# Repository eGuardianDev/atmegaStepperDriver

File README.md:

# atmegaStepperDriver  
  Open source stepper driver powered by Atmega chip

## Quick Description
This project was design to be used in my [Modul3D](https://github.com/eGuardianDev/Modul3D) project.
Now It has its own project.  
The idea to have simple, cheap, open source stepper driver for stepper motor

## Features and design   
- Powered by Atmega chip (at the moment Atmega328)  
- H-Bridge design  
- Flyback Voltage protection  
- Standart stepper driver communication  
- I2C communcation interface
- Fan controll

## Current Development
### Firmware
 - [ ] Todo...
### Hardware
#### Power
- [X] Power supply for the chip
- [X] Sepreate connection for power for the motor
- [X] Pins for power
#### Main system
- [X] H-bridge configuration
- [X] Connect the pins to the transistor of H-bridge
- [X] Calculate transistor resistor values
#### Communication
- [X] Pins for communication
- [X] I2C pins
- [X] Address Changer
- [ ] Step mode (maybe in next version or firmware based)
#### Protection
- [X] Add capacitor before transitor for smooth curves, but don't test it
- [X] Flyback protection (with ziner diode) 
- [X] Power supply smoothing and return diode
- [ ] Fully test protection system
#### Misc.
- [X] Change diode foot print

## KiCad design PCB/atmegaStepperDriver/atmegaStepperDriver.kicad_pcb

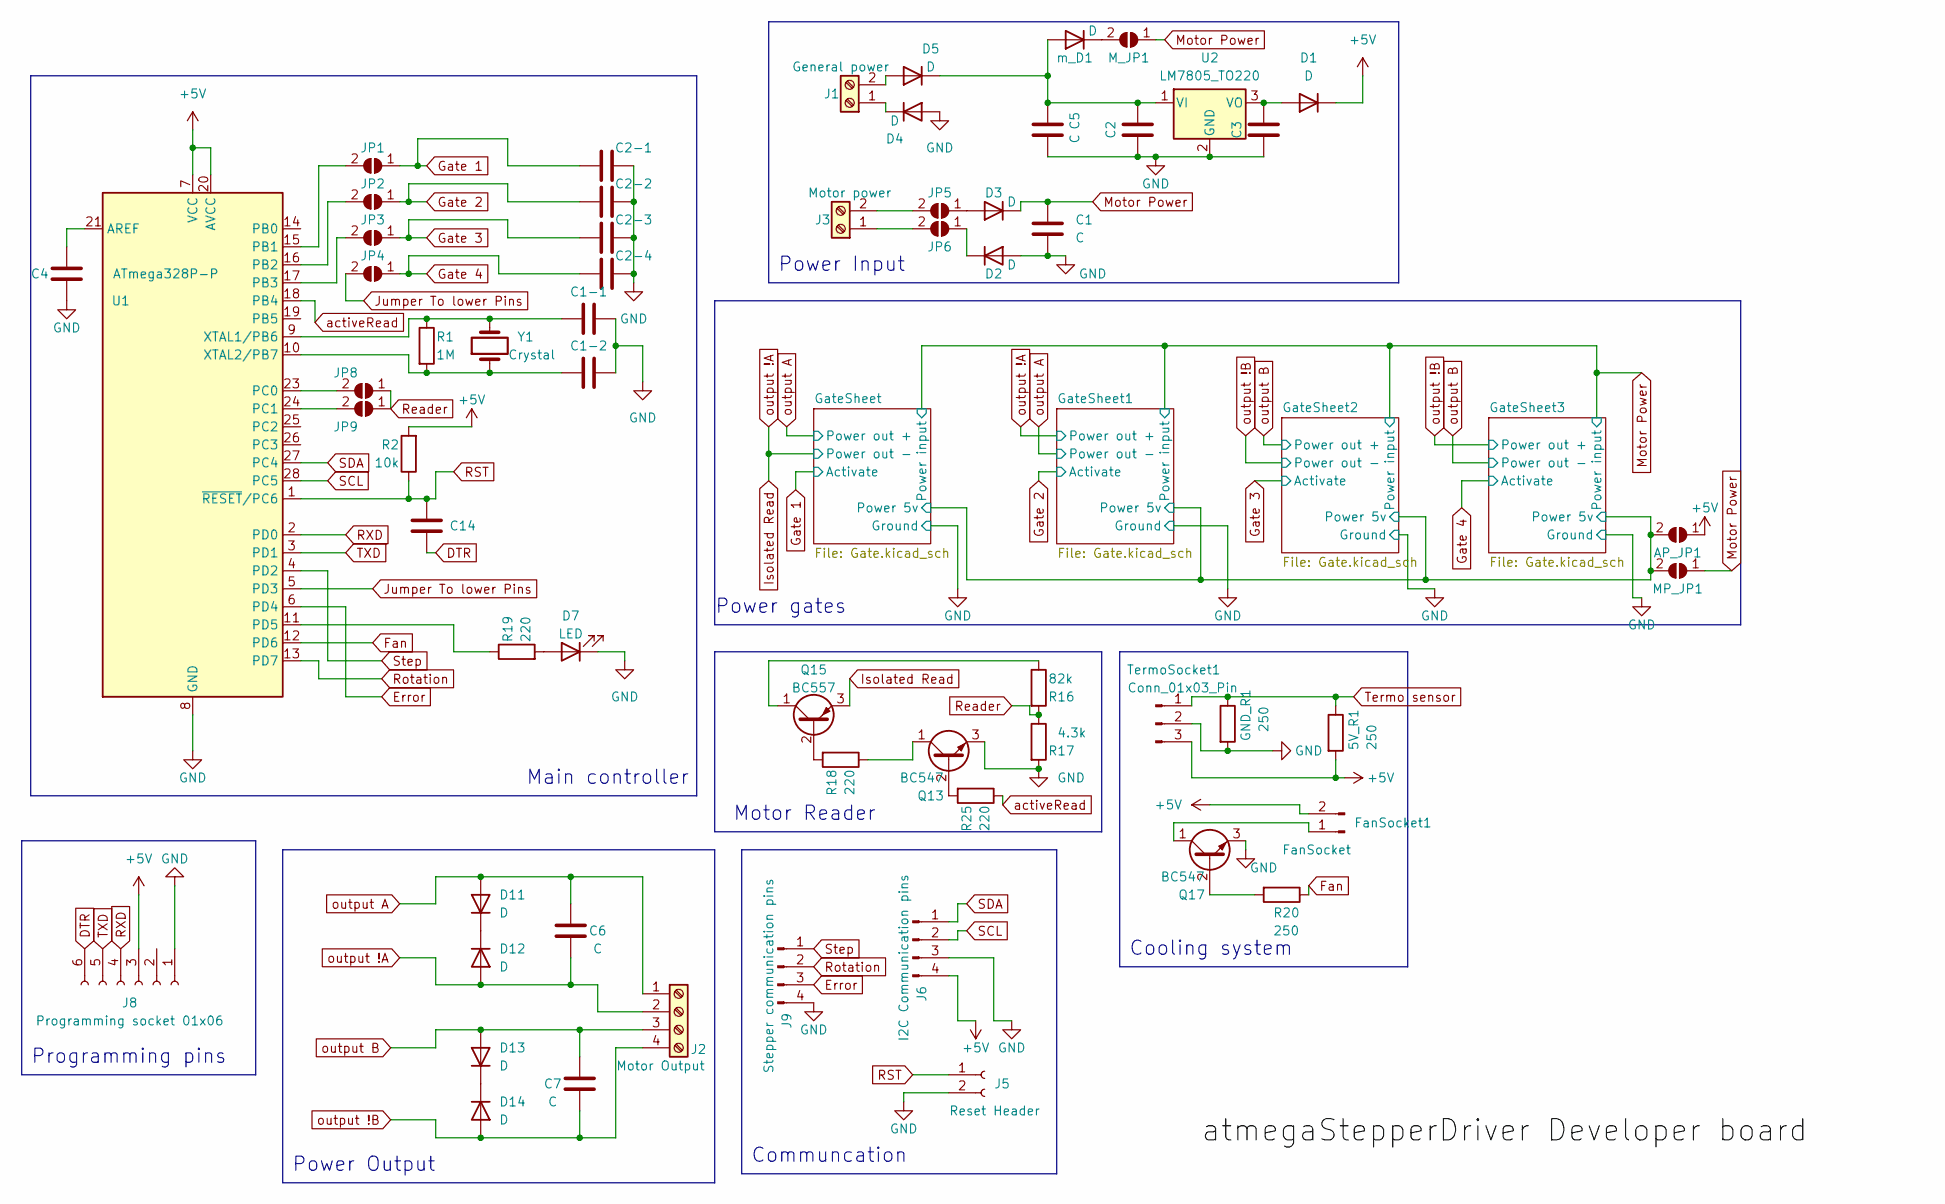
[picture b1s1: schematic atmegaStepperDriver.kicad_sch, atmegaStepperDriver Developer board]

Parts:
5V_R1: 250; R_Axial_DIN0207_L6.3mm_D2.5mm_P10.16mm_Horizontal
AP_JP1: SolderJumper_2_Open; SolderJumper-2_P1.3mm_Open_RoundedPad1.0x1.5mm
C1, C2-1, C2-2, C2-3, C2-4: C; CP_Radial_D8.0mm_P3.80mm
C1-1, C1-2, C2, C3, C4, C6, C7, C14: C; C_Disc_D5.0mm_W2.5mm_P2.50mm
C5: C; CP_Radial_D10.0mm_P5.00mm
D1, D2, D3, D4, D5, D11, D12, D13, D14: D; D_A-405_P7.62mm_Horizontal
D7: LED; LED_D5.0mm
FanSocket1: FanSocket; PinHeader_1x02_P2.54mm_Vertical
GND_R1: 250; R_Axial_DIN0207_L6.3mm_D2.5mm_P10.16mm_Horizontal
J1: General power; TerminalBlock_Phoenix_MKDS-1,5-2_1x02_P5.00mm_Horizontal
J2: Motor Output; TerminalBlock_bornier-4_P5.08mm
J3: Motor power; TerminalBlock_Phoenix_MKDS-1,5-2_1x02_P5.00mm_Horizontal
J5: Reset Header; PinHeader_1x02_P2.54mm_Vertical
J6: I2C Communication pins; PinHeader_1x04_P2.54mm_Vertical
J8: Programming socket 01x06; PinHeader_1x06_P2.54mm_Vertical
J9: Stepper communication pins; PinHeader_1x04_P2.54mm_Vertical
JP1, JP2, JP3, JP4, JP5, JP6, JP8, JP9: SolderJumper_2_Open; SolderJumper-2_P1.3mm_Open_RoundedPad1.0x1.5mm
MP_JP1: SolderJumper_2_Open; SolderJumper-2_P1.3mm_Open_RoundedPad1.0x1.5mm
M_JP1: SolderJumper_2_Open; SolderJumper-2_P1.3mm_Open_RoundedPad1.0x1.5mm
Q13, Q17: BC547; TO-92_Inline
Q15: BC557; TO-92_Inline
R1: 1M; R_Axial_DIN0207_L6.3mm_D2.5mm_P10.16mm_Horizontal
R2: 10k; R_Axial_DIN0207_L6.3mm_D2.5mm_P10.16mm_Horizontal
R16: 82k; R_Axial_DIN0207_L6.3mm_D2.5mm_P10.16mm_Horizontal
R17: 4.3k; R_Axial_DIN0207_L6.3mm_D2.5mm_P10.16mm_Horizontal
R18, R19, R25: 220; R_Axial_DIN0207_L6.3mm_D2.5mm_P10.16mm_Horizontal
R20: 250; R_Axial_DIN0207_L6.3mm_D2.5mm_P10.16mm_Horizontal
TermoSocket1: Conn_01x03_Pin; PinHeader_1x03_P2.54mm_Vertical
U1: ATmega328P-P; DIP-28_W7.62mm
U2: LM7805_TO220; TO-220-3_Vertical
Y1: Crystal; Crystal_HC49-U_Vertical
m_D1: D; D_A-405_P7.62mm_Horizontal

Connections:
+5V: 5V_R1.2, AP_JP1.1 (A), D1.1 (K), FanSocket1.2, J6.4, J8.3, R2.2, TermoSocket1.3, U1.7 (VCC), U1.20 (AVCC)
/GateSheet/Power 5v: AP_JP1.2 (B), MP_JP1.2 (B); also elsewhere on the board
DTR: C14.1, J8.6
Error: J9.3, U1.6 (PD4)
Fan: R20.1, U1.12 (PD6)
GND: C1.2, C1-1.2, C1-2.2, C2.1, C2-1.2, C2-2.2, C2-3.2, C2-4.2, C3.1, C4.1, C5.2, D2.2 (A), D4.2 (A), D7.1 (K), GND_R1.2, J5.2, J6.3, J8.1, J9.4, Q13.3 (E), Q17.3 (E), R17.2, TermoSocket1.2, U1.8 (GND), U1.22 (GND), U2.2 (GND); also elsewhere on the board
Gate 1: C2-1.1, JP1.1 (A); also elsewhere on the board
Gate 2: C2-2.1, JP2.1 (A); also elsewhere on the board
Gate 3: C2-3.1, JP3.1 (A); also elsewhere on the board
Gate 4: C2-4.1, JP4.1 (A); also elsewhere on the board
Isolated Read: C6.1, D12.2 (A), J2.2, Q15.3 (E); also elsewhere on the board
Jumper To lower Pins: JP4.2 (B), U1.5 (PD3)
Motor Power: C1.1, D3.1 (K), MP_JP1.1 (A), M_JP1.1 (A); also elsewhere on the board
unnamed: C3.2, D1.2 (A), U2.3 (VO)
unnamed: D2.1 (K), JP6.1 (A)
unnamed: D3.2 (A), JP5.1 (A)
unnamed: D4.1 (K), J1.1
unnamed: D5.2 (A), J1.2
unnamed: C2.2, C5.1, D5.1 (K), U2.1 (VI), m_D1.2 (A)
unnamed: D7.2 (A), R19.2
unnamed: D11.1 (K), D12.1 (K)
unnamed: D13.1 (K), D14.1 (K)
unnamed: FanSocket1.1, Q17.1 (C)
unnamed: J3.1, JP6.2 (B)
unnamed: J3.2, JP5.2 (B)
unnamed: JP1.2 (B), U1.15 (PB1)
unnamed: JP2.2 (B), U1.16 (PB2)
unnamed: JP3.2 (B), U1.17 (PB3)
unnamed: JP8.2 (B), U1.23 (PC0)
unnamed: JP9.2 (B), U1.24 (PC1)
unnamed: M_JP1.2 (B), m_D1.1 (K)
unnamed: Q13.2 (B), R25.2
unnamed: Q13.1 (C), R18.1
unnamed: Q15.2 (B), R18.2
unnamed: Q15.1 (C), R16.1
unnamed: Q17.2 (B), R20.2
unnamed: C4.2, U1.21 (AREF)
unnamed: R19.1, U1.11 (PD5)
unnamed: C1-1.1, R1.1, U1.9 (XTAL1/PB6), Y1.2
unnamed: C1-2.1, R1.2, U1.10 (XTAL2/PB7), Y1.1
RST: C14.2, J5.1, R2.1, U1.1 (~RESET/PC6)
RXD: J8.4, U1.2 (PD0)
Reader: JP8.1 (A), JP9.1 (A), R16.2, R17.1
Rotation: J9.2, U1.13 (PD7)
SCL: J6.2, U1.28 (PC5)
SDA: J6.1, U1.27 (PC4)
Step: J9.1, U1.4 (PD2)
TXD: J8.5, U1.3 (PD1)
Termo sensor: 5V_R1.1, GND_R1.1, TermoSocket1.1
activeRead: R25.1, U1.18 (PB4)
output !B: C7.1, D14.2 (A), J2.4; also elsewhere on the board
output A: C6.2, D11.2 (A), J2.1; also elsewhere on the board
output B: C7.2, D13.2 (A), J2.3; also elsewhere on the board

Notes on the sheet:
Main controller
Power Input
Programming pins
Communcation
Motor Reader
Cooling system
Power Output
Power gates

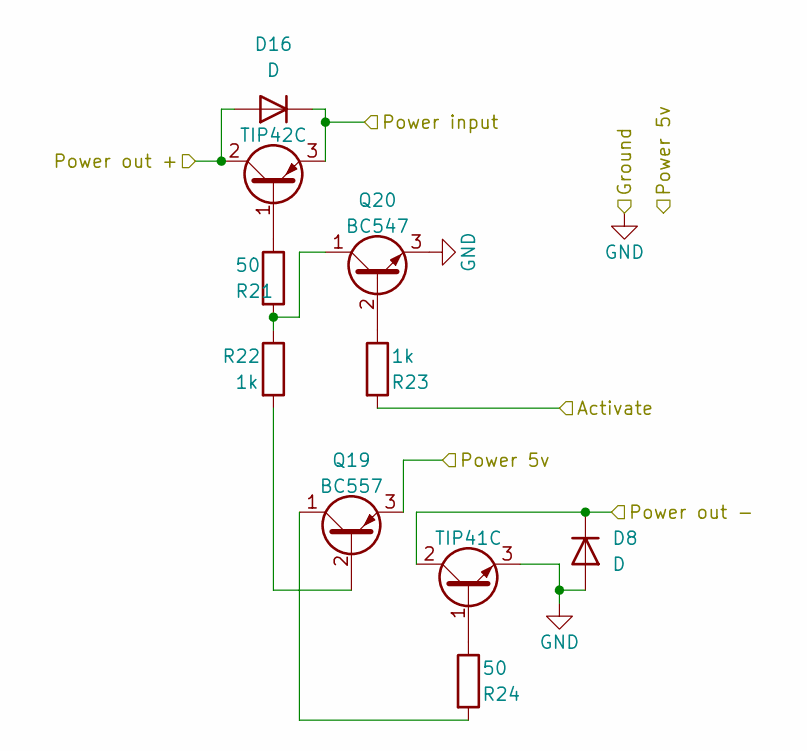
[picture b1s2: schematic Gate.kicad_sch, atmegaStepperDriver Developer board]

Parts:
D8, D16: D; D_DO-35_SOD27_P10.16mm_Horizontal
Q18: TIP42C; TO-220-3_Vertical
Q19: BC557; TO-92_Inline_Wide
Q20: BC547; TO-92_Inline_Wide
Q21: TIP41C; TO-220-3_Vertical
R21, R24: 50; R_Axial_DIN0207_L6.3mm_D2.5mm_P10.16mm_Horizontal
R22, R23: 1k; R_Axial_DIN0207_L6.3mm_D2.5mm_P10.16mm_Horizontal

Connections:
/GateSheet/Power 5v: Q19.3 (E); also elsewhere on the board
GND: D8.2 (A), Q20.3 (E), Q21.3 (E); also elsewhere on the board
Gate 1: R23.2; also elsewhere on the board
Isolated Read: D8.1 (K), Q21.2 (C); also elsewhere on the board
Motor Power: D16.1 (K), Q18.3 (E); also elsewhere on the board
unnamed: Q18.1 (B), R21.1
unnamed: Q19.2 (B), R22.2
unnamed: Q19.1 (C), R24.2
unnamed: Q20.2 (B), R23.1
unnamed: Q20.1 (C), R21.2, R22.1
unnamed: Q21.1 (B), R24.1
output A: D16.2 (A), Q18.2 (C); also elsewhere on the board

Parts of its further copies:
D9, D10, D15, D17, D18, D19: D; D_DO-35_SOD27_P10.16mm_Horizontal
Q1, Q5, Q9: TIP42C; TO-220-3_Vertical
Q2, Q6, Q10: BC557; TO-92_Inline_Wide
Q3, Q7, Q11: BC547; TO-92_Inline_Wide
Q4, Q8, Q12: TIP41C; TO-220-3_Vertical
R3, R6, R7, R10, R11, R14: 50; R_Axial_DIN0207_L6.3mm_D2.5mm_P10.16mm_Horizontal
R4, R5, R8, R9, R12, R13: 1k; R_Axial_DIN0207_L6.3mm_D2.5mm_P10.16mm_Horizontal

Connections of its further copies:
/GateSheet/Power 5v: Q2.3 (E), Q6.3 (E), Q10.3 (E); also elsewhere on the board
GND: D9.2 (A), D10.2 (A), D15.2 (A), Q3.3 (E), Q4.3 (E), Q7.3 (E), Q8.3 (E), Q11.3 (E), Q12.3 (E); also elsewhere on the board
Gate 2: R5.2; also elsewhere on the board
Gate 3: R9.2; also elsewhere on the board
Gate 4: R13.2; also elsewhere on the board
Isolated Read: D17.2 (A), Q1.2 (C); also elsewhere on the board
Motor Power: D17.1 (K), D18.1 (K), D19.1 (K), Q1.3 (E), Q5.3 (E), Q9.3 (E); also elsewhere on the board
unnamed: Q1.1 (B), R3.1
unnamed: Q2.2 (B), R4.2
unnamed: Q2.1 (C), R6.2
unnamed: Q3.2 (B), R5.1
unnamed: Q3.1 (C), R3.2, R4.1
unnamed: Q4.1 (B), R6.1
unnamed: Q5.1 (B), R7.1
unnamed: Q6.2 (B), R8.2
unnamed: Q6.1 (C), R10.2
unnamed: Q7.2 (B), R9.1
unnamed: Q7.1 (C), R7.2, R8.1
unnamed: Q8.1 (B), R10.1
unnamed: Q9.1 (B), R11.1
unnamed: Q10.2 (B), R12.2
unnamed: Q10.1 (C), R14.2
unnamed: Q11.2 (B), R13.1
unnamed: Q11.1 (C), R11.2, R12.1
unnamed: Q12.1 (B), R14.1
output !B: D10.1 (K), D19.2 (A), Q8.2 (C), Q9.2 (C); also elsewhere on the board
output A: D9.1 (K), Q4.2 (C); also elsewhere on the board
output B: D15.1 (K), D18.2 (A), Q5.2 (C), Q12.2 (C); also elsewhere on the board

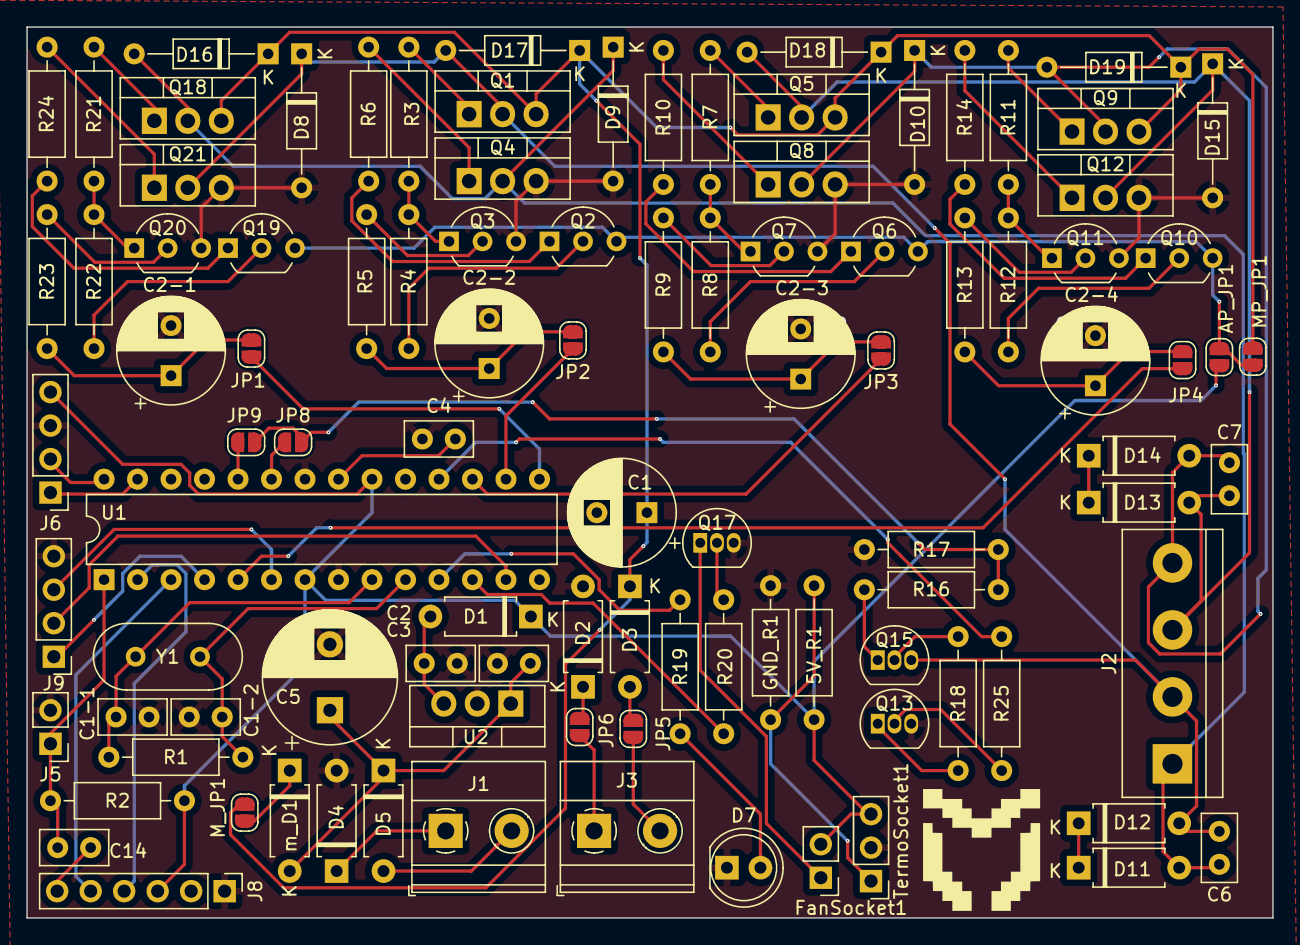
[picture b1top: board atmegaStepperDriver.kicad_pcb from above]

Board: 2 copper layers, 94.5 x 67.6 mm, 101 parts (0 on the bottom side), 77 nets.

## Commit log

2023-07-28 Quick information update
2023-07-29 pcb design; unfinished;
2023-07-29 gitignore;
2023-07-31 added seprate power supply box; tested protection circuit; added inputs for power;
2023-07-31 added programmable pins; fixed footprints; removed old protection; separated few sectors
2023-08-03 pcb desing started; lower level transistors added; fast pwm tested
2023-08-06 Todo system organized; more to be added;
2023-08-06 Typo fix; some todo list fix
2023-08-06 communication pins;
2023-08-07 General design ready; footprints ready; V0.0.5
2023-08-07 change capacitor footprint; added few pictures;
2023-08-07 All general connections ready; further check needed; V0.0.6
2023-08-07 added pictures
2023-08-09 Footprint done; ready for testing; drc clear; Gerber files;V0.7.1;
2023-08-09 Update todo list
2023-08-10 Updated pictures to new version
2023-08-13 Typo
2023-08-25 new design; the old one doesn't work; to be finished;
2023-08-29 fixed old design flaw; full redisgn; Few things to be done; V0.8.0;
2023-08-29 traces fixed; fan added; V0.8.1
2023-08-30 added transistor for fan; final checks; Gerber files ready; V0.8.2
2023-08-30 changed version on board back
2023-09-15 fixed bad transistors; readme; V0.8.3
2024-03-29 posible fix, need more research + for the streak
2024-04-01 Fix gate; added termistor; gate sheet added; v0.8.4
2024-04-03 Reader for motor movement added; possible resistor on termistor
2024-04-04 Added analog read for motor error
2024-09-04 someData; idk what i did, forgot to push it
